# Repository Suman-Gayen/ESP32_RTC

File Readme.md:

# ESP32 RTC Clock Display Project Documentation

## Project Overview

This project is an ESP32-based Real Time Clock (RTC) display system designed using KiCad EDA. The circuit combines an ESP32-WROOM-32 microcontroller, DS3231M RTC module, MAX7219 display driver, and 4-digit 7-segment display for accurate real-time clock measurement and display.

The project provides:

- Accurate real-time clock functionality
- Battery-backed timekeeping
- 7-segment LED display output
- Push button controls
- UART programming interface
- LED status indicators
- Stable regulated power supply

---

# 1. System Architecture

The project is divided into the following major sections:

1. Power Supply Section
2. ESP32 Microcontroller Section
3. RTC (Real Time Clock) Section
4. Display Driver Section
5. 7-Segment Display Section
6. Push Button Interface
7. Status LED Interface
8. UART Programming Interface

---

# 2. Main Components Used

| Component | Part Number | Function |
|---|---|---|
| Microcontroller | ESP32-WROOM-32 | Main processing unit |
| RTC IC | DS3231M | Accurate real-time clock |
| Display Driver | MAX7219 | 7-segment display controller |
| Voltage Regulator | AMS1117 | 3.3V power regulation |
| Display | CC56-12SRWA | 7-segment LED display |
| Battery | Coin Cell | RTC backup power |
| LEDs | Generic LEDs | Status indication |
| Push Buttons | SW_Push | User input control |
| Capacitors | Electrolytic & Ceramic | Filtering and stabilization |
| Resistors | Various | Pull-up, current limiting, biasing |

---

# 3. Working Principle of the Project

The system operates by continuously reading real-time data from the DS3231M RTC module using I2C communication. The ESP32 processes the received time information and sends display data to the MAX7219 display driver through SPI communication.

The MAX7219 controls the multiplexed 7-segment display and updates the visible time output.

The RTC module maintains accurate timing even during power loss because of the backup battery.

Buttons are used for reset, boot, or user interaction functions.

LED indicators provide system status feedback.

---

# 4. Detailed Explanation of Major Components

## 4.1 ESP32-WROOM-32 Microcontroller

### Function
The ESP32 is the main controller of the entire system.

### Main Responsibilities

- Reads time from RTC
- Processes clock data
- Sends display data to MAX7219
- Handles button inputs
- Controls LEDs
- Manages communication protocols

### Features

- Dual-core processor
- Built-in WiFi and Bluetooth
- Multiple GPIO pins
- SPI support
- I2C support
- UART programming interface
- Low power operation
---

## 4.2 DS3231M RTC Module

### Function
The DS3231M maintains accurate date and time information.

### Working

- Uses internal crystal oscillator
- Keeps time continuously
- Communicates with ESP32 using I2C
- Uses backup battery during power failure

### Important Pins

| Pin | Function |
|---|---|
| SDA | I2C Data Line |
| SCL | I2C Clock Line |
| VBAT | Backup Battery Input |
| SQW | Square Wave Output |
| RST | Reset Pin |

---

## 4.3 MAX7219 Display Driver

### Function
The MAX7219 controls the 7-segment display using serial communication.

### Working

- Receives serial data from ESP32
- Controls multiplexing automatically
- Reduces GPIO usage
- Controls brightness internally

### Communication Interface

SPI Communication:

| Signal | Function |
|---|---|
| DIN | Data Input |
| CLK | Clock Signal |
| LOAD | Chip Select |

---

## 4.4 AMS1117 Voltage Regulator

### Function
Converts input voltage to stable 3.3V output.

### Working

- Accepts higher DC input voltage
- Regulates output to 3.3V
- Filters voltage fluctuations
- Protects ESP32 from overvoltage

### Capacitors Used

| Capacitor | Purpose |
|---|---|
| Input Capacitor | Input filtering |
| Output Capacitor | Output stabilization |

---

## 4.5 7-Segment Display (CC56-12SRWA)

### Function
Displays real-time clock information visually.

### Working

The display receives segment control signals from MAX7219 and displays numbers accordingly.

### Segments

| Segment | Description |
|---|---|
| A-G | Numeric display segments |
| DP | Decimal Point |

---

# 5. Power Supply Section

## Components Used

- AMS1117 Regulator
- Capacitors
- Power Flags
- Battery Backup

## Working

The input supply voltage is regulated to 3.3V for ESP32 and RTC operation.

Capacitors remove voltage ripple and improve power stability.

The RTC battery ensures time retention during power failure.

---

# 6. RTC Communication Section

## Communication Type

I2C Communication

## Signals

| Signal | Description |
|---|---|
| SDA | Serial Data |
| SCL | Serial Clock |

## Pull-up Resistors

4.7k pull-up resistors are used because I2C lines require pull-up configuration.

### Why Pull-up Resistors Are Necessary?

- I2C uses open-drain outputs
- Prevents floating signals
- Ensures proper logic HIGH level
- Improves communication reliability

---

# 7. Display Communication Section

## Communication Type

SPI Communication

## Signals Used

| Signal | Description |
|---|---|
| DIN | Serial Data |
| CLK | Clock |
| LOAD | Latch/Chip Select |

## Working

ESP32 sends serial display data to MAX7219.

MAX7219 converts serial data into segment control outputs.

---

# 8. Push Button Section

## Buttons Used

| Button | Function |
|---|---|
| RESET | System Reset |
| BOOT | Programming Mode |

## Working

Buttons provide manual user control.

Pull-up resistors maintain stable logic levels.

---

# 9. LED Indicator Section

## LEDs Used

- Power LED
- Status LED

## Working

LEDs indicate:

- Power status
- System operation
- Communication activity

Current-limiting resistors protect LEDs from excess current.

---

# 10. Important Resistors and Their Purpose

| Resistor | Purpose |
|---|---|
| 4.7k | I2C pull-up resistors |
| 10k | Pull-up/pull-down configuration |
| 220Ω | LED current limiting |
| 1k | Signal conditioning |

---

# 11. Capacitors Used in the Circuit

| Capacitor | Purpose |
|---|---|
| 0.1uF | Noise filtering |
| 10uF | Power stabilization |
| 22uF | Bulk filtering |
| 1uF | Decoupling |

---

# 12. Advantages of This Project

- Accurate timekeeping
- Battery backup support
- Compact PCB design
- Low GPIO usage
- Expandable architecture
- Wireless-capable controller
- Stable power regulation
- Bright display output

---

# 13. Applications of This Project

- Digital clocks
- Industrial timer systems
- Embedded timing systems
- IoT time synchronization projects
- Smart display systems
- Automation systems

---

# 14. Conclusion

This ESP32 RTC Clock Display project demonstrates a complete embedded system combining:

- Real-time clock functionality
- SPI and I2C communication
- LED display driving
- Power regulation
- User interface control

The design is efficient, reliable, scalable, and suitable for embedded system learning and practical applications.

The combination of ESP32, DS3231M, and MAX7219 creates a modern and powerful RTC display system with excellent accuracy and expandability.

---

# 15. Reference Schematic Information

Project Name: Real Time Clock Measurement

Design Tool: KiCad EDA 9.0.2

Main Modules:

- ESP32-WROOM-32
- DS3231M RTC
- MAX7219 Display Driver
- AMS1117 Regulator
- CC56-12SRWA Display

---

# End of Documentation

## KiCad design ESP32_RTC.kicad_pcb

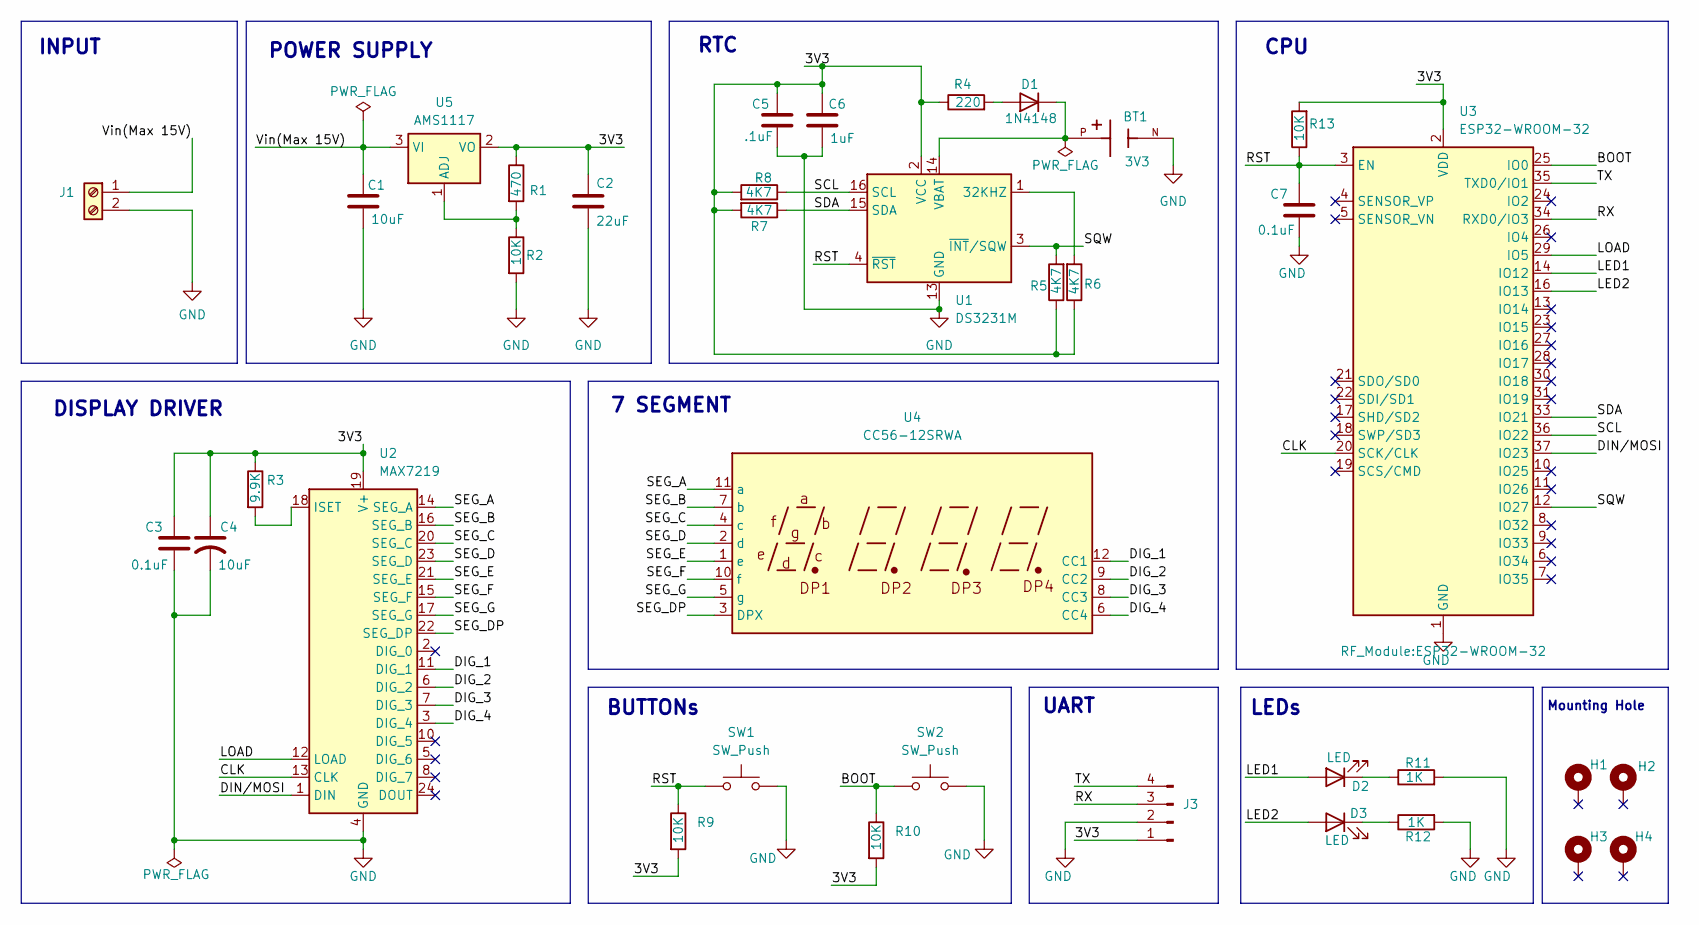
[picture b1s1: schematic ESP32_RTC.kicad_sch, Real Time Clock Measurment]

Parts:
BT1: 3V3; BAT_1072; PARTREV A
C1, C4: 10uF; C_0805_2012Metric
C2: 22uF; C_0805_2012Metric
C3, C7: 0.1uF; C_0805_2012Metric
C5: .1uF; C_0805_2012Metric
C6: 1uF; C_0805_2012Metric
D1: 1N4148; D_DO-41_SOD81_P2.54mm_Vertical_KathodeUp
D2, D3: LED; LED_0805_2012Metric
H1, H2, H3, H4: MountingHole_Pad; MountingHole_2.2mm_M2_Pad_Via
J1: Screw_Terminal_01x02; TerminalBlock_bornier-2_P5.08mm
J3: Conn_01x04_Pin; PinHeader_1x04_P2.54mm_Vertical
R1: 470; R_0805_2012Metric
R2, R9, R10, R13: 10K; R_0805_2012Metric
R3: 9.9K; R_0805_2012Metric
R4: 220; R_0805_2012Metric
R5, R6, R7, R8: 4K7; R_0805_2012Metric
R11, R12: 1K; R_0805_2012Metric
SW1, SW2: SW_Push; SW_PUSH_6mm
U1: DS3231M; SOIC-16W_7.5x10.3mm_P1.27mm
U2: MAX7219; SOIC-24W_7.5x15.4mm_P1.27mm
U3: ESP32-WROOM-32
U4: CC56-12SRWA; DIP-16_W7.62mm_Socket
U5: AMS1117; SOT-223-3_TabPin2

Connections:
/3V3: C2.1, C3.1, C4.1, C5.1, C6.1, J3.1, R1.1, R3.1, R4.1, R5.1, R6.1, R7.2, R8.2, R9.2, R10.2, R13.2, U1.2 (VCC), U2.19 (V+), U3.2 (VDD), U5.2 (VO)
/BOOT: R10.1, SW2.1, U3.25 (IO0)
/CLK: U2.13 (CLK), U3.20 (SCK/CLK)
/DIG_1: U2.11 (DIG_1), U4.12 (CC1)
/DIG_2: U2.6 (DIG_2), U4.9 (CC2)
/DIG_3: U2.7 (DIG_3), U4.8 (CC3)
/DIG_4: U2.3 (DIG_4), U4.6 (CC4)
/DIN/MOSI: U2.1 (DIN), U3.37 (IO23)
/LED1: D2.2 (A), U3.14 (IO12)
/LED2: D3.2 (A), U3.16 (IO13)
/LOAD: U2.12 (LOAD), U3.29 (IO5)
/RST: C7.1, R9.1, R13.1, SW1.1, U1.4 (~RST), U3.3 (EN)
/RX: J3.3, U3.34 (RXD0/IO3)
/SCL: R8.1, U1.16 (SCL), U3.36 (IO22)
/SDA: R7.1, U1.15 (SDA), U3.33 (IO21)
/SEG_A: U2.14 (SEG_A), U4.11 (a)
/SEG_B: U2.16 (SEG_B), U4.7 (b)
/SEG_C: U2.20 (SEG_C), U4.4 (c)
/SEG_D: U2.23 (SEG_D), U4.2 (d)
/SEG_DP: U2.22 (SEG_DP), U4.3 (DPX)
/SEG_E: U2.21 (SEG_E), U4.1 (e)
/SEG_F: U2.15 (SEG_F), U4.10 (f)
/SEG_G: U2.17 (SEG_G), U4.5 (g)
/SQW: R5.2, U1.3 (~INT/SQW), U3.12 (IO27)
/TX: J3.4, U3.35 (TXD0/IO1)
/Vin(Max 15V): C1.1, J1.1, U5.3 (VI)
GND: BT1.N, C1.2, C2.2, C3.2, C4.2, C5.2, C6.2, C7.2, J1.2, J3.2, R2.2, R11.2, R12.2, SW1.2, SW2.2, U1.5 (GND), U1.6 (GND), U1.7 (GND), U1.8 (GND), U1.9 (GND), U1.10 (GND), U1.11 (GND), U1.12 (GND), U1.13 (GND), U2.4 (GND), U2.9 (GND), U3.1 (GND), U3.15 (GND), U3.38 (GND), U3.39 (GND)
unnamed: D1.2 (A), R4.2
unnamed: BT1.P, D1.1 (K), U1.14 (VBAT)
unnamed: D2.1 (K), R11.1
unnamed: D3.1 (K), R12.1
unnamed: R6.2, U1.1 (32KHZ)
unnamed: R3.2, U2.18 (ISET)
unnamed: R1.2, R2.1, U5.1 (ADJ)

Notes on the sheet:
Mounting Hole
CPU
DISPLAY DRIVER
LEDs
RTC
7 SEGMENT
INPUT
UART
POWER SUPPLY
BUTTONs

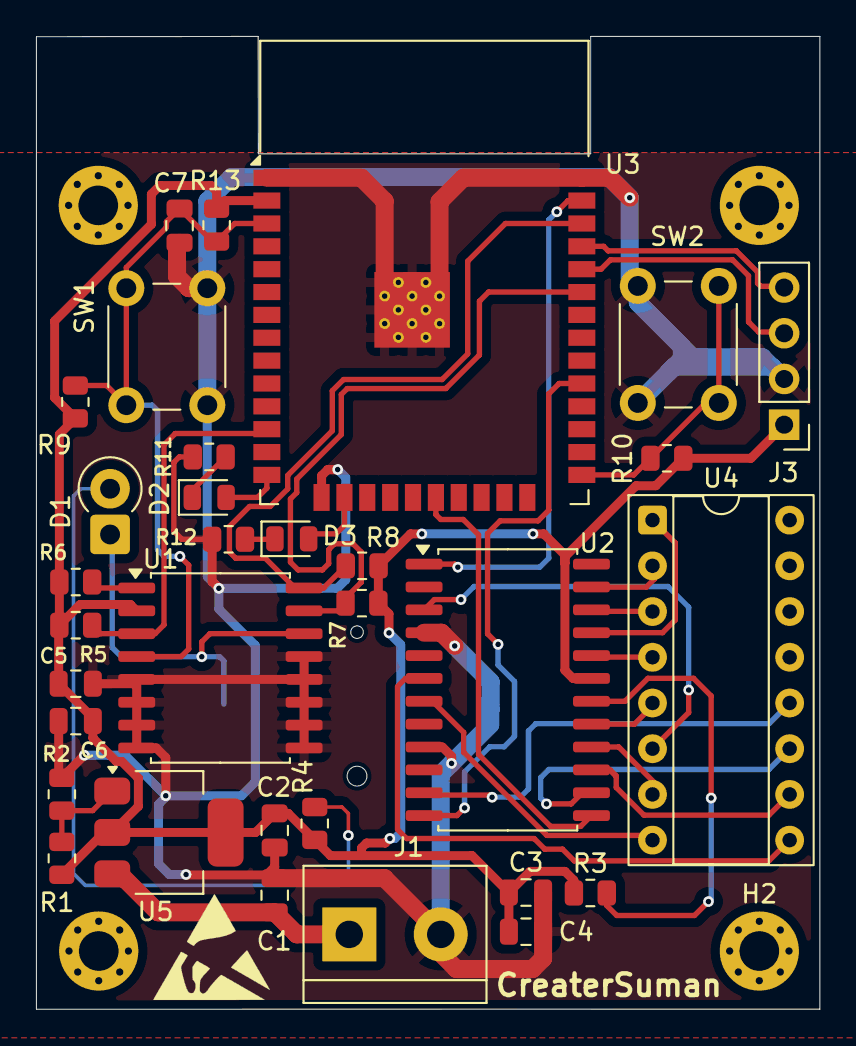
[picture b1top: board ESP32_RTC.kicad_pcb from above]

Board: 2 copper layers, 43.5 x 54.0 mm, 37 parts (1 on the bottom side), 34 nets.

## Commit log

2026-05-23 Refactor Readme by removing component comparisons and conclusionsreadme update
    Removed comparison sections and conclusions for various components in the Readme file, and updated section titles for better clarity.
2026-05-25 image update
